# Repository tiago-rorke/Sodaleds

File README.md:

##[Sodaleds](http://www.tiago.co.nz/sodaleds.html)

Modular rectangular LED construction kit. Simple pcb frames allow blocks of 8 leds to be easily powered by a 7.4V source such as a 2-cell Lithium polymer battery.

Contributed to the 2013 Open Mobile project coordinated by [Rita Sá](http://www.rita-sa.com/index.html), with help from [Alt-lab](http://altlab.org/).

All design files licensed under the terms of the [Creative Commons Attribution-NonCommercial-ShareAlike License.](http://creativecommons.org/licenses/by-nc-sa/3.0/legalcode)

###Parts List

Each panel (7 boards) requires 56 LEDs, and 14 resistors.
*	LEDs Rectangular, 5 x 2 x 7mm:
	-	Red - [Digi-Key 754-1201-ND](http://www.digikey.co.uk/product-detail/en/WP113IDT/754-1201-ND/1747600)
	-	Green - [Digi-Key 754-1200-ND](http://www.digikey.com/product-detail/en/WP113GDT/754-1200-ND/1747599)
	-	Yellow - [Digi-Key 754-1203-ND](http://www.digikey.com/product-detail/en/WP113YDT/754-1203-ND/1747602)
*	130Ω 3mm Resistors - [Digi-Key S130QCT-ND](http://www.digikey.com/product-detail/en/CFM14JT130R/S130QCT-ND/2617670)
*	You will need a 7.4V power source, such as a 2-cell lipo battery and a charger.
	-	[HobbyKing Turnigy 500mAh 2S 20C](http://hobbyking.com/hobbyking/store/__9187__Turnigy_500mAh_2S_20C_Lipo_Pack.html)
	-	[HobbyKing B3AC Compact Charger](http://hobbyking.com/hobbyking/store/__22410__HobbyKing_B3AC_Compact_Charger.html)
*	Hook up wire.  A bundle of short, tinned multicore wires would be ideal [such as these](http://www.dhgate.com/product/enameled-wire-23mm-1mm-black-short-wire-welding/143403910.html), but i made my own.  Short jumper wires could work but may be too stiff.
*	For assembling the boards together, wire wrap works well, otherwise small zip ties can work.  String would probably work well.

**Take Note!**
The boards will get a little bit warm when on.  Take this into consideration when arranging the boards so as to avoid putting too much current through a single board.

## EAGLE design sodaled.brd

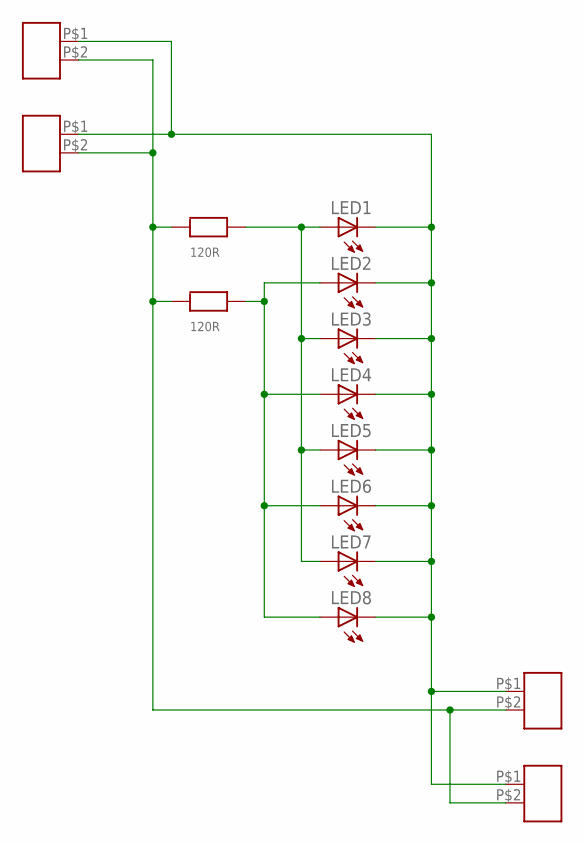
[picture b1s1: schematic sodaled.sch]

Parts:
LED1, LED2, LED3, LED4, LED5, LED6, LED7, LED8: LEDRECT_SIDE; LED_RECT_SIDEMOUNT
U$1, U$2, U$3, U$4: M02; 1X02
U$7, U$8: 120R; RESISTOR_CFM1

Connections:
7.4V: U$1.P$2, U$2.P$2, U$3.P$2, U$4.P$2, U$7.P$1, U$8.P$1
GND: LED1.C, LED2.C, LED3.C, LED4.C, LED5.C, LED6.C, LED7.C, LED8.C, U$1.P$1, U$2.P$1, U$3.P$1, U$4.P$1
unnamed: LED1.A, LED3.A, LED5.A, LED7.A, U$7.P$2
unnamed: LED2.A, LED4.A, LED6.A, LED8.A, U$8.P$2

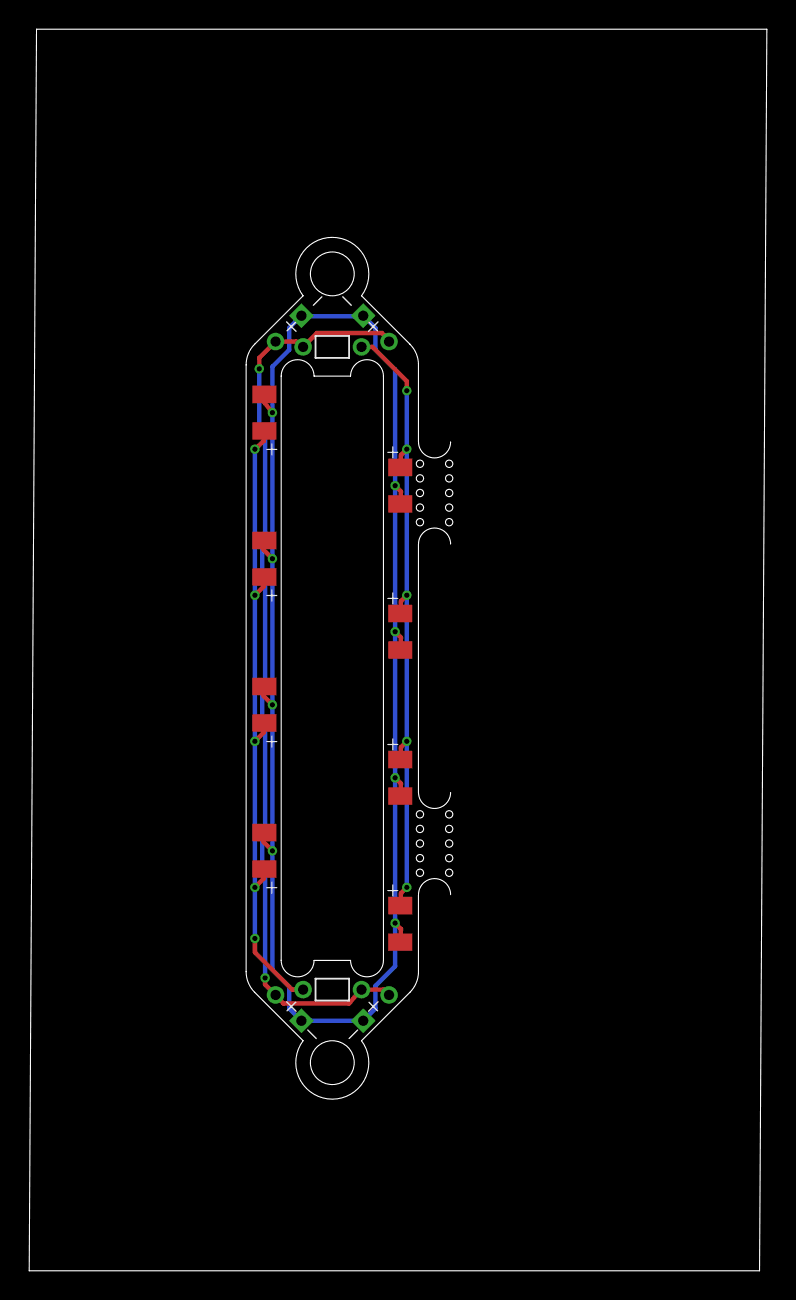
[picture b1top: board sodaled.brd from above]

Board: 2 copper layers, 50.5 x 85.0 mm, 14 parts (0 on the bottom side), 4 nets.

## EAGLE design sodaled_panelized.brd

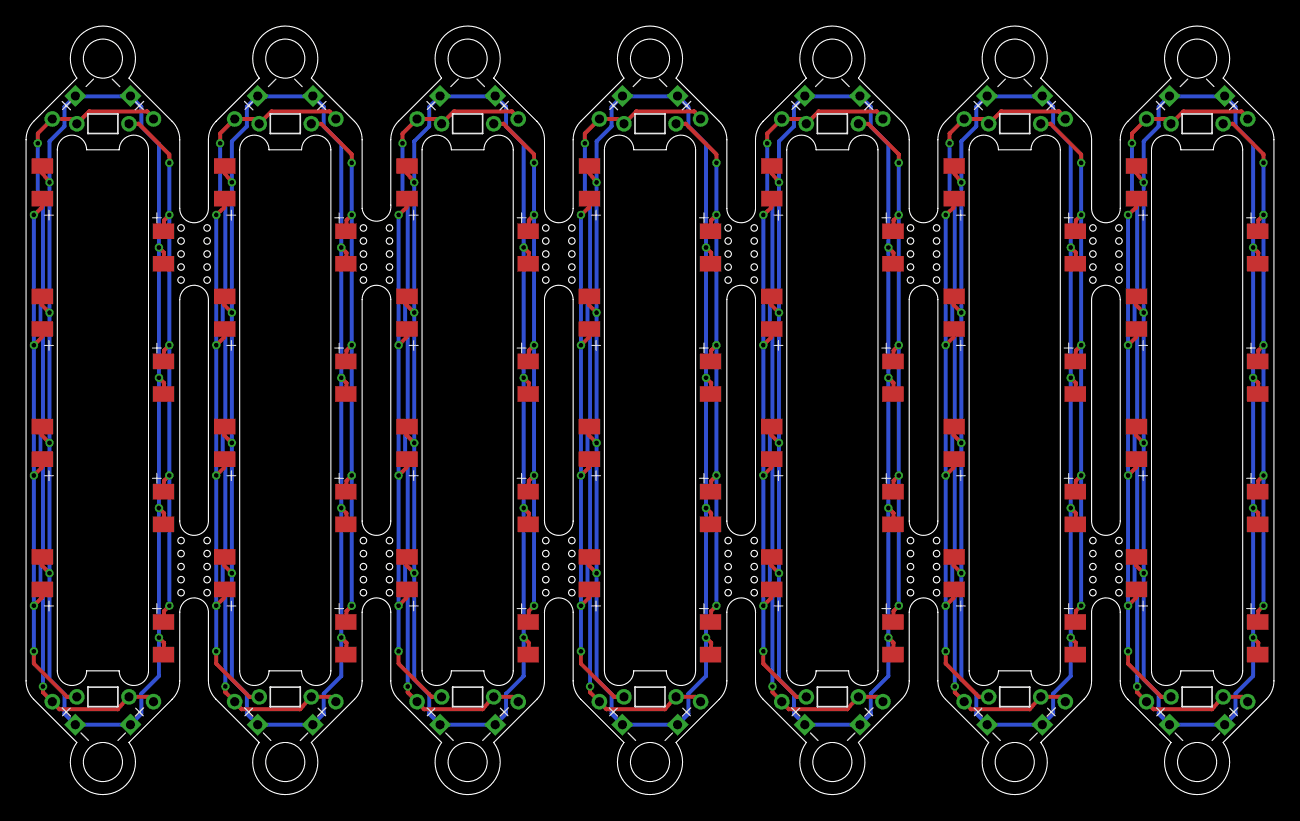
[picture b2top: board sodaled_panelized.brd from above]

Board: 2 copper layers, 95.8 x 59.0 mm, 98 parts (0 on the bottom side), 28 nets.

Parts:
LED1, LED2, LED3, LED4, LED5, LED6, LED7, LED8, LED9, LED10, LED11, LED12, LED13, LED14, LED15, LED16, LED17, LED18, LED19, LED20, LED21, LED22, LED23, LED24, LED25, LED26, LED27, LED28, LED29, LED30, LED31, LED32, LED33, LED34, LED35, LED36, LED37, LED38, LED39, LED40, LED41, LED42, LED43, LED44, LED45, LED46, LED47, LED48, LED49, LED50, LED51, LED52, LED53, LED54, LED55, LED56: LED_RECT_SIDEMOUNT
U$1, U$2, U$3, U$4, U$5, U$6, U$9, U$10, U$13, U$14, U$15, U$16, U$19, U$20, U$21, U$22, U$25, U$26, U$27, U$28, U$31, U$32, U$33, U$34, U$37, U$38, U$39, U$40: M02; 1X02
U$7, U$8, U$11, U$12, U$17, U$18, U$23, U$24, U$29, U$30, U$35, U$36, U$41, U$42: 120R; RESISTOR_CFM1

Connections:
7.4V: U$1.P$2, U$2.P$2, U$3.P$2, U$4.P$2, U$7.P$1, U$8.P$1
7.4V1: U$5.P$2, U$6.P$2, U$9.P$2, U$10.P$2, U$11.P$1, U$12.P$1
7.4V2: U$13.P$2, U$14.P$2, U$15.P$2, U$16.P$2, U$17.P$1, U$18.P$1
7.4V3: U$19.P$2, U$20.P$2, U$21.P$2, U$22.P$2, U$23.P$1, U$24.P$1
7.4V4: U$25.P$2, U$26.P$2, U$27.P$2, U$28.P$2, U$29.P$1, U$30.P$1
7.4V5: U$31.P$2, U$32.P$2, U$33.P$2, U$34.P$2, U$35.P$1, U$36.P$1
7.4V6: U$37.P$2, U$38.P$2, U$39.P$2, U$40.P$2, U$41.P$1, U$42.P$1
GND: LED1.C, LED2.C, LED3.C, LED4.C, LED5.C, LED6.C, LED7.C, LED8.C, U$1.P$1, U$2.P$1, U$3.P$1, U$4.P$1
GND1: LED9.C, LED10.C, LED11.C, LED12.C, LED13.C, LED14.C, LED15.C, LED16.C, U$5.P$1, U$6.P$1, U$9.P$1, U$10.P$1
GND2: LED17.C, LED18.C, LED19.C, LED20.C, LED21.C, LED22.C, LED23.C, LED24.C, U$13.P$1, U$14.P$1, U$15.P$1, U$16.P$1
GND3: LED25.C, LED26.C, LED27.C, LED28.C, LED29.C, LED30.C, LED31.C, LED32.C, U$19.P$1, U$20.P$1, U$21.P$1, U$22.P$1
GND4: LED33.C, LED34.C, LED35.C, LED36.C, LED37.C, LED38.C, LED39.C, LED40.C, U$25.P$1, U$26.P$1, U$27.P$1, U$28.P$1
GND5: LED41.C, LED42.C, LED43.C, LED44.C, LED45.C, LED46.C, LED47.C, LED48.C, U$31.P$1, U$32.P$1, U$33.P$1, U$34.P$1
GND6: LED49.C, LED50.C, LED51.C, LED52.C, LED53.C, LED54.C, LED55.C, LED56.C, U$37.P$1, U$38.P$1, U$39.P$1, U$40.P$1
unnamed: LED9.A, LED11.A, LED13.A, LED15.A, U$11.P$2
unnamed: LED1.A, LED3.A, LED5.A, LED7.A, U$7.P$2
unnamed: LED2.A, LED4.A, LED6.A, LED8.A, U$8.P$2
unnamed: LED10.A, LED12.A, LED14.A, LED16.A, U$12.P$2
unnamed: LED17.A, LED19.A, LED21.A, LED23.A, U$17.P$2
unnamed: LED18.A, LED20.A, LED22.A, LED24.A, U$18.P$2
unnamed: LED25.A, LED27.A, LED29.A, LED31.A, U$23.P$2
unnamed: LED26.A, LED28.A, LED30.A, LED32.A, U$24.P$2
unnamed: LED33.A, LED35.A, LED37.A, LED39.A, U$29.P$2
unnamed: LED34.A, LED36.A, LED38.A, LED40.A, U$30.P$2
unnamed: LED41.A, LED43.A, LED45.A, LED47.A, U$35.P$2
unnamed: LED42.A, LED44.A, LED46.A, LED48.A, U$36.P$2
unnamed: LED49.A, LED51.A, LED53.A, LED55.A, U$41.P$2
unnamed: LED50.A, LED52.A, LED54.A, LED56.A, U$42.P$2

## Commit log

2013-11-06 sodaleds!
2013-11-06 added CC-NC-SA license
2013-11-06 readme edit
2013-11-16 added parts list
2013-12-03 Create gh-pages branch via GitHub
